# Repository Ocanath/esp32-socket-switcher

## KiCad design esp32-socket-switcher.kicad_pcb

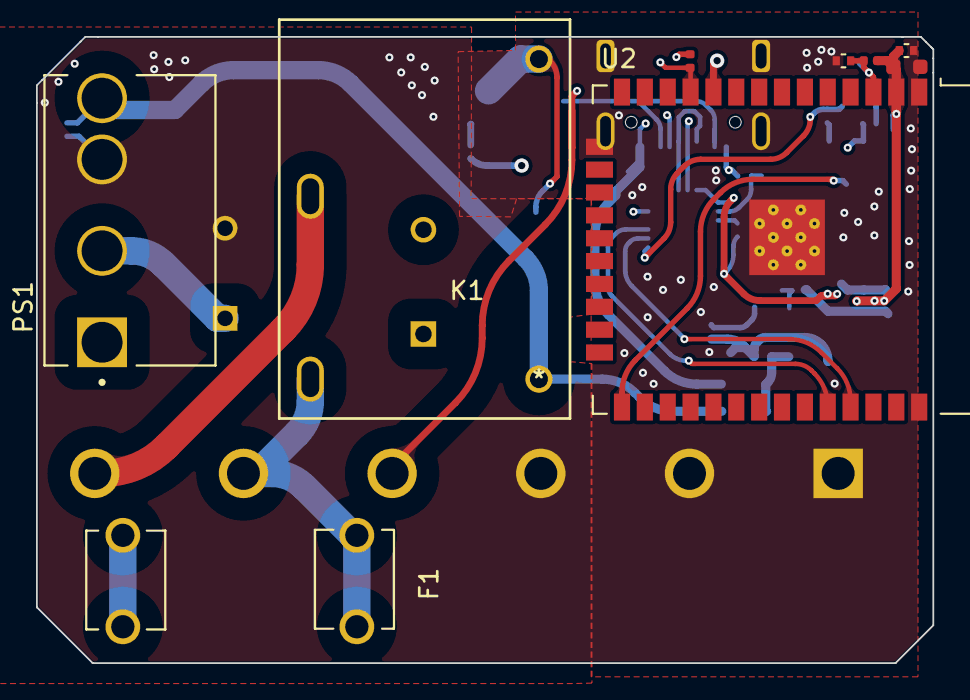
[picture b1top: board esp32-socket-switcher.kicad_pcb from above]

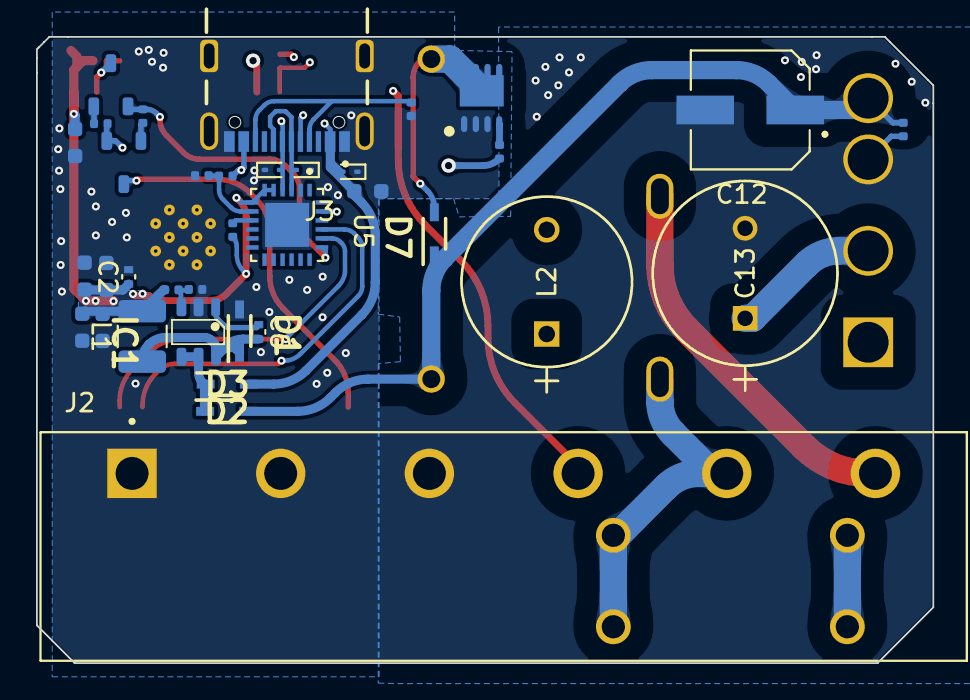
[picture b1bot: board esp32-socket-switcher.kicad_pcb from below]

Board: 4 copper layers, 49.8 x 34.8 mm, 45 parts (36 on the bottom side), 30 nets.

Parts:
C1, C3, C5, C7, C8, C10, C11: 4.7uF; C_0603_1608Metric
C2, C4, C6, C9: 100nF; C_0402_1005Metric
C12: EEE-FK1C221XP; CAP_EEEFK1C221XP
C13: UCY2G100MPD; U1-S_NCH
D1, D2, D3, D7: NSR0530HT1G; SOD2512X110N
D4, D5, D6: ESD9B3.3ST5G; D_SOD-923
F1: Fuse 1A/300V; FUSE_3519
IC1: ADP2301AUJZ-R7; SOT95P280X100-6N
J2: 4DB-P108-06; TE_2-1437667-9
J3: USB4105-GF-A; GCT_USB4105-GF-A
K1: G5CA-1A DC5; RELAY_G5CA_OMR
L1: 2.2uH; L_1210_3225Metric
L2: RLB1014-122KL; IND_BOURNS_RLB1014
PS1: LS01-K3B05SS; CONV_LS01-K3B05SS
Q1, Q2: SS8050-G; SOT-23-3
Q3: CSD17575Q3T; 8-PowerVDFN
R1, R2, R6, R10, R13: 10k; R_0402_1005Metric
R3: 1k; R_0402_1005Metric
R4: 22k; R_0402_1005Metric
R5: 31.6k; R_0402_1005Metric
R7: 5.1k; R_0402_1005Metric
R9: 47.5k; R_0402_1005Metric
R11: 10.2k; R_0402_1005Metric
R12: 10; R_0402_1005Metric
U2: ESP32-WROOM-32E-H4; ESP32-WROOM-32
U5: CP2102N-A02-GQFN24R; QFN50P400X400X80-25N

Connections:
3v3: C1.1, C2.1, C3.1, C4.1, C7.1, C8.1, C10.1, C11.1, L1.2, R3.2, R5.2, R6.2, R13.1, U2.2 (3V3), U5.5 (VIO), U5.6 (VDD), U5.7 (VREGIN)
/3V3-Supply/FB: IC1.3 (FB), R5.1, R11.2
/3V3-Supply/VIN: D2.1 (K), D3.1 (K), IC1.4 (EN), IC1.5 (VIN)
/AC_LIVE: F1.1, J2.5, K1.4
/AC_LIVE_SWITCHED: J2.6, K1.3
/D+: D5.2 (A2), J3.A6 (DP1), J3.B6 (DP2), U5.3 (D+)
/D-: D6.2 (A2), J3.A7 (DN1), J3.B7 (DN2), U5.4 (D-)
/ESP32/CP210x_RX: U2.35 (TXD0), U5.20 (RXD)
/ESP32/CP210x_TX: U2.34 (RXD0), U5.21 (TXD)
/ESP32/CP210x_VBUS: R4.1, R9.2, U5.8 (VBUS)
/ESP32/DTR: Q2.2 (E), R2.1, U5.23 (~DTR)
/ESP32/EN: C9.1, Q1.3 (C), R6.1, U2.3 (EN)
/ESP32/IO0: Q2.3 (C), U2.25 (IO0)
/ESP32/RELAY_OUT: R12.1, U2.10 (IO25)
/ESP32/RTS: Q1.2 (E), R1.1, U5.19 (~RTS)
/SWITCH_IN: J2.4, R13.2, U2.11 (IO26)
/VDC-WALL: C12.1, D2.2 (A), D7.1 (K), K1.1, PS1.4 (+VO), R10.2
/VUSB: C5.1, D3.2 (A), D4.2 (A2), J3.A4_B9 (VBUS), J3.B4_A9 (VBUS__1), R4.2
GND: C1.2, C2.2, C3.2, C4.2, C5.2, C7.2, C8.2, C9.2, C10.2, C11.2, C12.2, C13.2, D1.2 (A), D4.1 (A1), D5.1 (A1), D6.1 (A1), IC1.2 (GND), J2.1, J2.2, J2.3, J3.A1_B12 (GND), J3.B1_A12 (GND__1), J3.SH1 (SHELL_GND), J3.SH2 (SHELL_GND__1), J3.SH3 (SHELL_GND__2), J3.SH4 (SHELL_GND__3), PS1.3 (AC(N)/-VO), Q3.1 (S), R7.1, R9.1, R10.1, R11.1, U2.1 (GND), U2.15 (GND), U2.38 (GND), U2.39 (P_GND), U5.2 (GND), U5.25 (GND__1)
unnamed: C6.2, D1.1 (K), IC1.6 (SW), L1.1
unnamed: D7.2 (A), K1.2, Q3.3 (D)
unnamed: F1.2, L2.1
unnamed: C6.1, IC1.1 (BST)
unnamed: J3.A5 (CC1), J3.B5 (CC2), R7.2
unnamed: C13.1, PS1.2 (+V(CAP))
unnamed: L2.2, PS1.1 (AC(L))
unnamed: Q1.1 (B), R2.2
unnamed: Q2.1 (B), R1.2
unnamed: Q3.2 (G), R12.2
unnamed: R3.1, U5.9 (~RST)

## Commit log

2024-04-14 copy out precursor pcb from robot cortex, diverging to here
2024-04-14 some placement and IMPORTANT schematic mistake fix from heirarchichal label importing
2024-04-14 mains to relay lable
2024-04-14 added symbols for screw terminals
2024-04-14 some routing. need to add the things
2024-04-14 added screw terms. think i need a barrier block instead...
2024-04-14 swtiched to barrier block
2024-04-14 added caps and placed them
2024-04-14 added fuse. I feel i have been deceived...
2024-04-14 added IRM to lib unlinked 3d, gonna place
2024-04-14 changed inductors, sticking with og converter
2024-04-14 routing
2024-04-14 routed
2024-04-15 chamfered the corners , so u kno its real
2024-04-15 re-layed out a much larger board which is designed to fit into a 1gang socket. wonder if the wifi will make it out the boxxxxx
2024-04-15 updated fuse, generating gerber, about to flag a bunch as no bom for jlc order cuz this one is gonna be a pain in the ass to assemble
2024-04-15 updated usbc connector to one that's ACTUALLY FUCKING IN STOCK
2024-04-15 teardrops and curvy traces
